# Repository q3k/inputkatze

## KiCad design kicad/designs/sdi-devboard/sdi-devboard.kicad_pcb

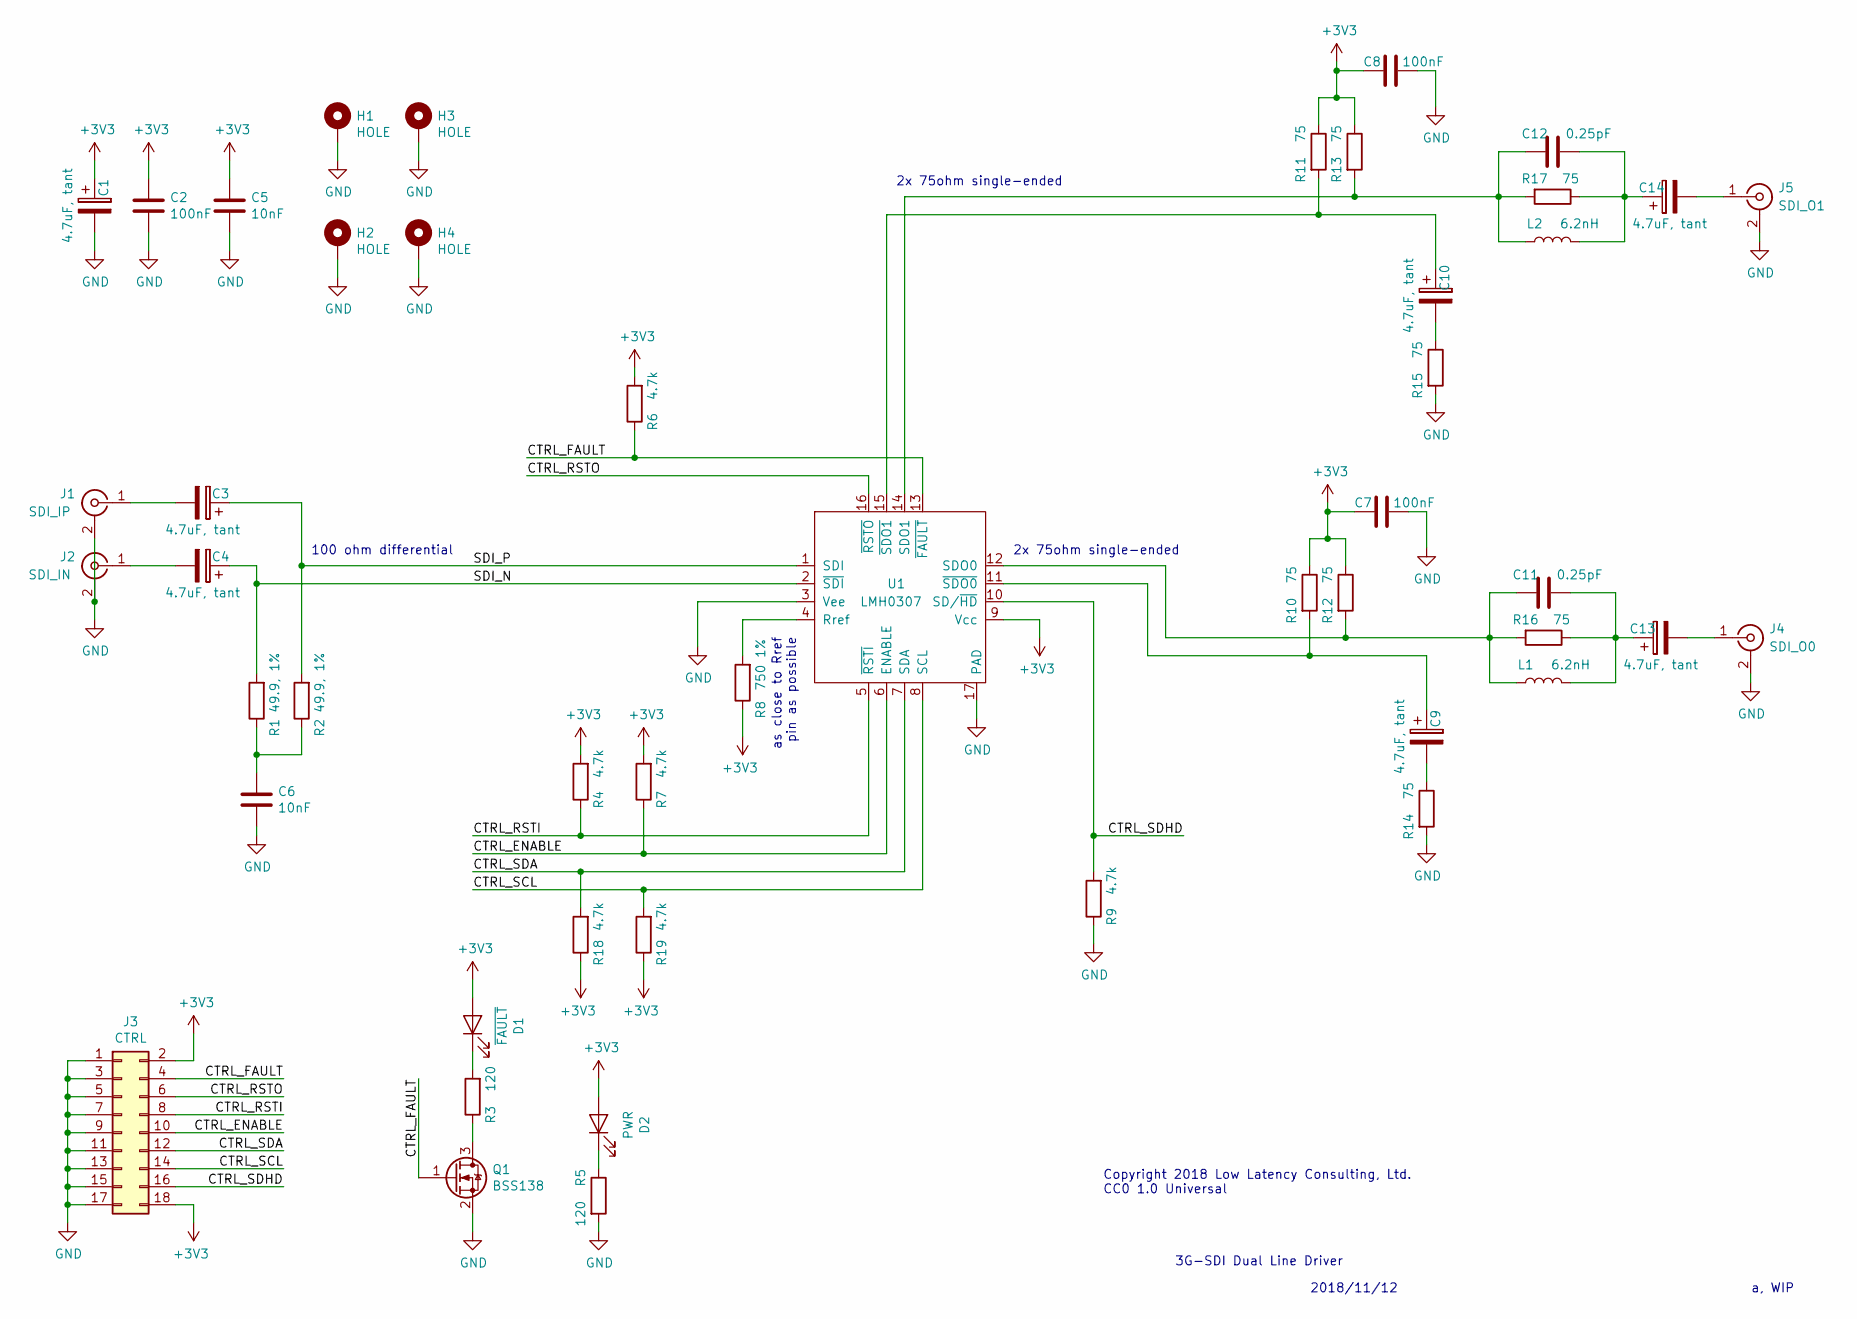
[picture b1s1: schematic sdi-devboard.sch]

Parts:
C1, C3, C4, C9, C10, C13, C14: 4.7uF, tant; CP_EIA-1608-08_AVX-J
C2, C7, C8: 100nF; C_0603_1608Metric
C5, C6: 10nF; C_0603_1608Metric
C11, C12: 0.25pF; C_0603_1608Metric
D1: ~FAULT; LED_0603_1608Metric
D2: PWR; LED_0603_1608Metric
H1, H2, H3, H4: HOLE; MountingHole_3.2mm_M3_DIN965_Pad
J1: SDI_IP; SMA_Molex_73251-1153_EdgeMount_Horizontal
J2: SDI_IN; SMA_Molex_73251-1153_EdgeMount_Horizontal
J3: CTRL; PinHeader_2x09_P2.54mm_Vertical
J4: SDI_O0; molex-bnc-73171-1640
J5: SDI_O1; molex-bnc-73171-1640
L1, L2: 6.2nH; L_0603_1608Metric
Q1: BSS138; SOT-23
R1, R2: 49.9, 1%; R_0603_1608Metric
R3, R5: 120; R_0603_1608Metric
R4, R6, R7, R9, R18, R19: 4.7k; R_0603_1608Metric
R8: 750 1%; R_0603_1608Metric
R10, R11, R12, R13, R14, R15, R16, R17: 75; R_0603_1608Metric
U1: LMH0307; WQFN-16-1EP_4x4mm_P0.65mm_EP2.1x2.1mm_ThermalVias

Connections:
+3V3: C1.1, C2.1, C5.1, C7.1, C8.1, D1.2 (A), D2.2 (A), J3.2, J3.18, R4.2, R6.2, R7.2, R8.1, R10.1, R11.1, R12.1, R13.1, R18.1, R19.1, U1.9 (Vcc)
/CTRL_ENABLE: J3.10, R7.1, U1.6 (ENABLE)
/CTRL_FAULT: J3.4, Q1.1 (G), R6.1, U1.13 (~FAULT)
/CTRL_RSTI: J3.8, R4.1, U1.5 (~RSTI)
/CTRL_RSTO: J3.6, U1.16 (~RSTO)
/CTRL_SCL: J3.14, R19.2, U1.8 (SCL)
/CTRL_SDA: J3.12, R18.2, U1.7 (SDA)
/CTRL_SDHD: J3.16, R9.2, U1.10 (SD/~HD)
/SDI_N: C4.1, R1.2, U1.2 (~SDI)
/SDI_P: C3.1, R2.2, U1.1 (SDI)
GND: C1.2, C2.2, C5.2, C6.2, C7.2, C8.2, H1.1, H2.1, H3.1, H4.1, J1.2 (Ext), J2.2 (Ext), J3.1, J3.3, J3.5, J3.7, J3.9, J3.11, J3.13, J3.15, J3.17, J4.2 (Ext), J5.2 (Ext), Q1.2 (S), R5.2, R9.1, R14.2, R15.2, U1.3 (Vee), U1.17 (PAD)
unnamed: C3.2, J1.1 (In)
unnamed: C4.2, J2.1 (In)
unnamed: C6.1, R1.1, R2.1
unnamed: C9.1, R10.2, U1.11 (~SDO0)
unnamed: C9.2, R14.1
unnamed: C10.1, R11.2, U1.15 (~SDO1)
unnamed: C10.2, R15.1
unnamed: C11.1, C13.1, L1.2, R16.1
unnamed: C11.2, L1.1, R12.2, R16.2, U1.12 (SDO0)
unnamed: C12.1, C14.1, L2.2, R17.1
unnamed: C12.2, L2.1, R13.2, R17.2, U1.14 (SDO1)
unnamed: C13.2, J4.1 (In)
unnamed: C14.2, J5.1 (In)
unnamed: D1.1 (K), R3.2
unnamed: D2.1 (K), R5.1
unnamed: Q1.3 (D), R3.1
unnamed: R8.2, U1.4 (Rref)

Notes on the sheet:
3G-SDI Dual Line Driver
Copyright 2018 Low Latency Consulting, Ltd. CC0 1.0 Universal
a, WIP
2018/11/12
as close to Rref pin as possible
100 ohm differential
2x 75ohm single-ended

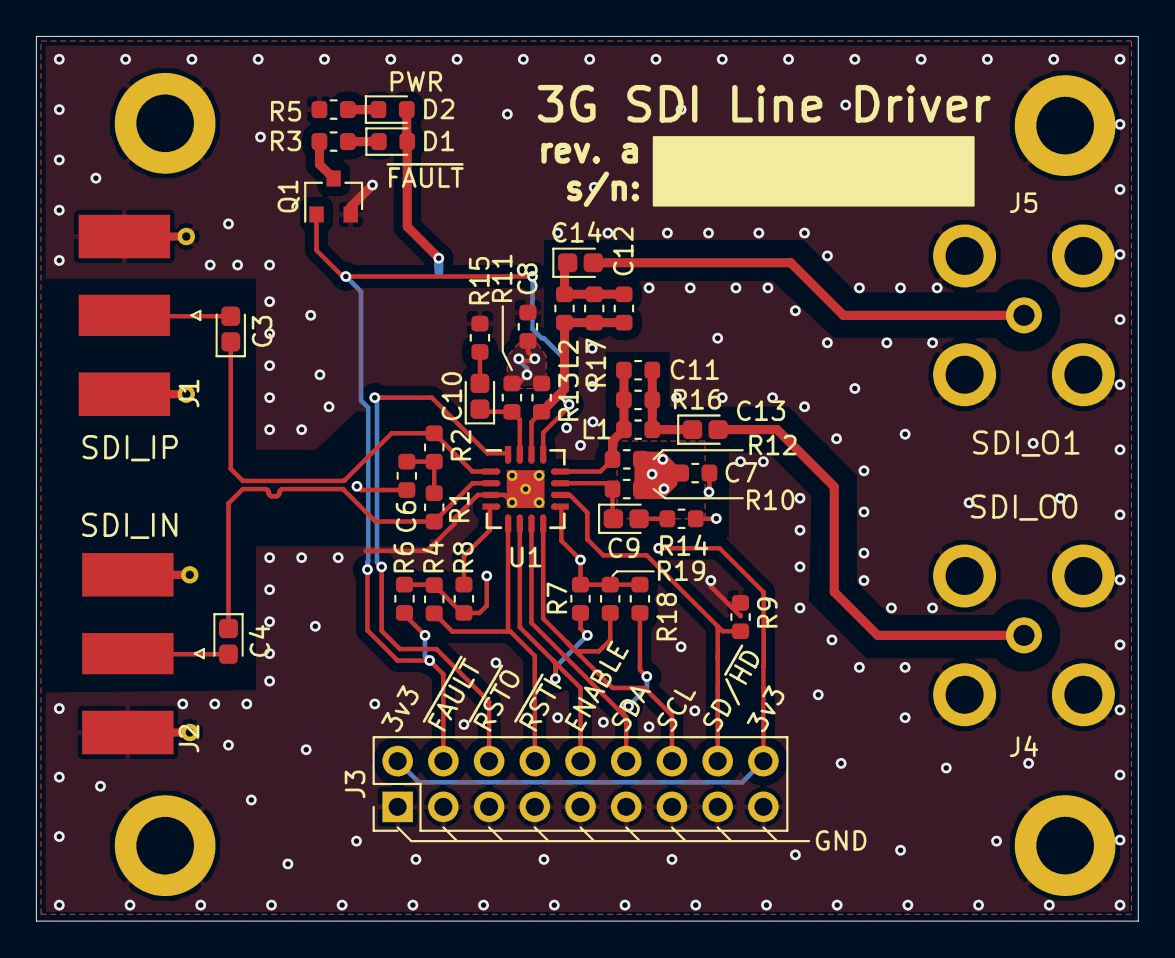
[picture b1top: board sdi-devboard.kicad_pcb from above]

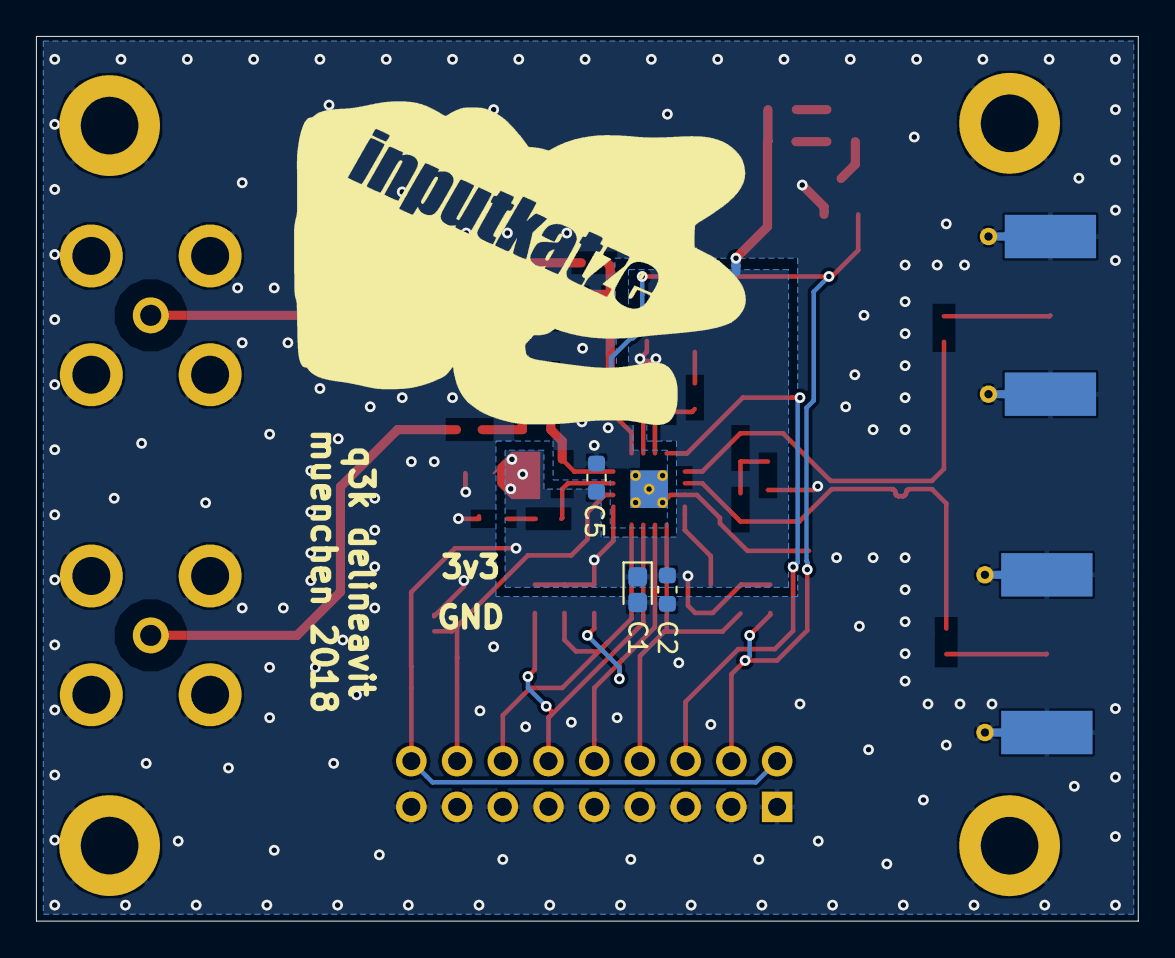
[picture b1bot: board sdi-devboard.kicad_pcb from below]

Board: 2 copper layers, 61.2 x 49.1 mm, 48 parts (3 on the bottom side), 28 nets.

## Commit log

2018-11-19 initial (empty) commit
2018-11-20 Preliminary requirements
2018-11-22 Import upstream kicad symbols, footprints and modules
2018-11-22 Add local footprints and symbols
2018-11-22 Add sdi-devboard
2018-11-22 Cut revA for sdi-devboard
